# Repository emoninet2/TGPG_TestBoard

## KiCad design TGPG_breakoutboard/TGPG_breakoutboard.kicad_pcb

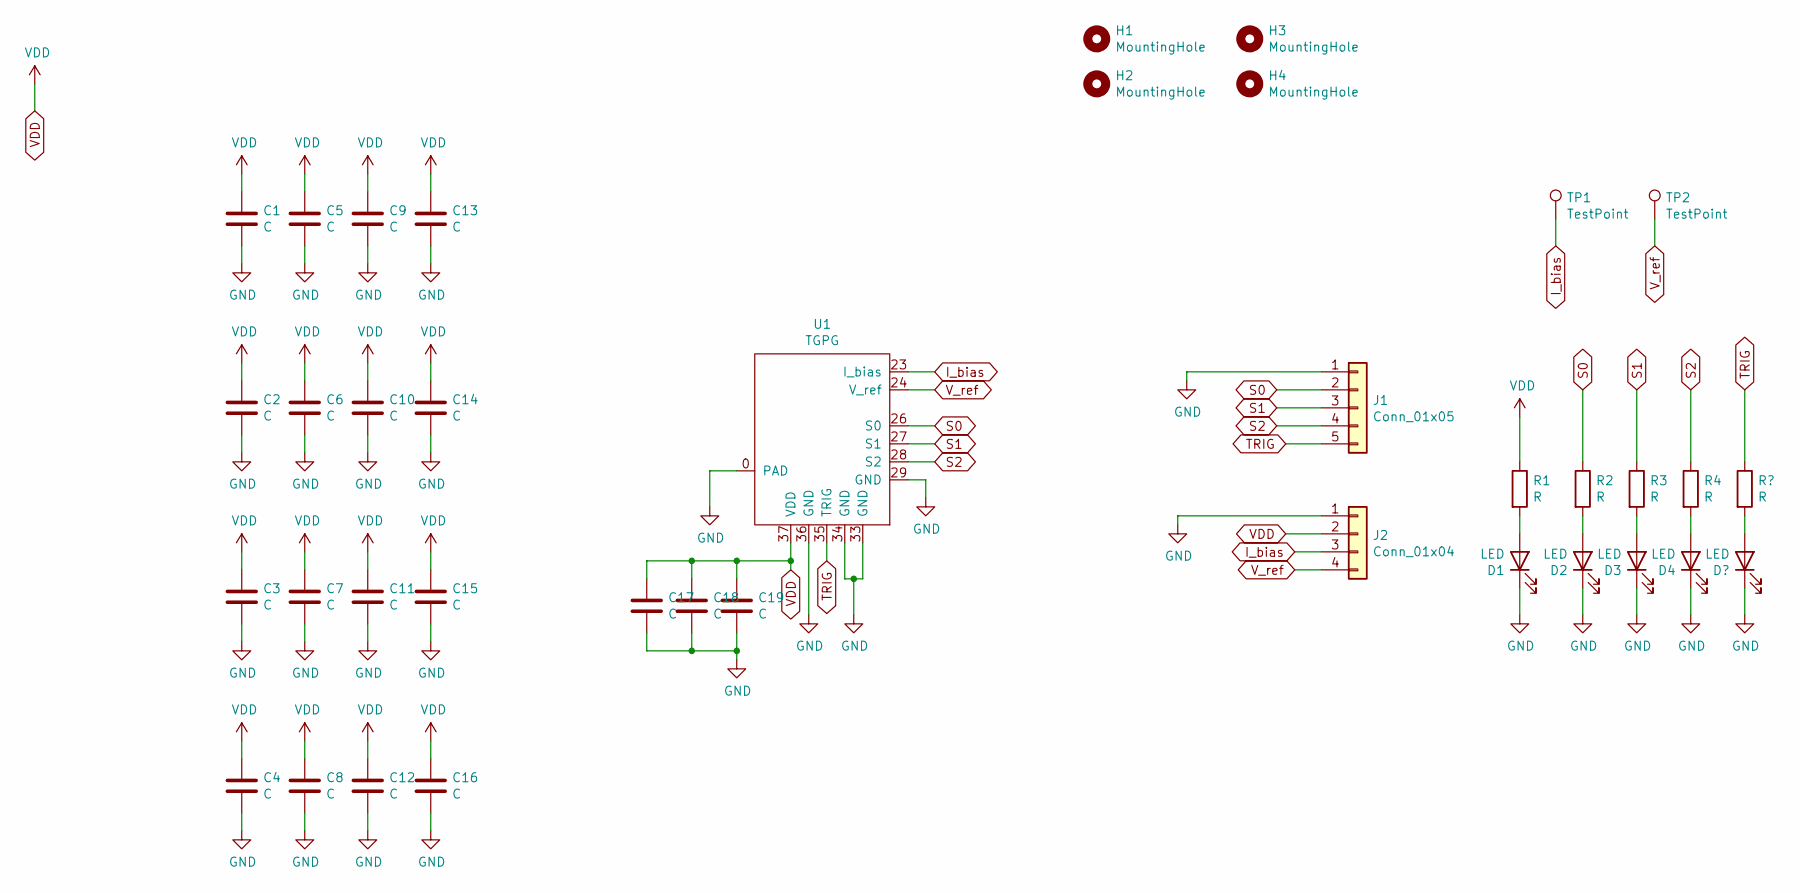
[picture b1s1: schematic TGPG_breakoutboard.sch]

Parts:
C1, C2, C3, C4, C5, C6, C7, C8, C9, C10, C11, C12, C13, C14, C15, C16, C17, C18, C19: C; C_0402_1005Metric
D1, D2, D3, D4: LED; LED_0402_1005Metric
H1, H2, H3, H4: MountingHole; MountingHole_5.5mm_Pad
J1: Conn_01x05; PinHeader_1x05_P2.54mm_Vertical
J2: Conn_01x04; PinHeader_1x04_P2.54mm_Vertical
R1, R2, R3, R4: R; R_0402_1005Metric
TP1, TP2: TestPoint; TestPoint_Pad_1.0x1.0mm
U1: TGPG; Master_w2020

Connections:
GND: C1.2, C2.2, C3.2, C4.2, C5.2, C6.2, C7.2, C8.2, C9.2, C10.2, C11.2, C12.2, C13.2, C14.2, C15.2, C16.2, C17.2, C18.2, C19.2, D1.1 (K), D2.1 (K), D3.1 (K), D4.1 (K), J1.1, J2.1, U1.0 (PAD), U1.29 (GND), U1.33 (GND), U1.34 (GND), U1.36 (GND); also elsewhere on the board
I_bias: J2.3, TP1.1, U1.23 (I_bias)
unnamed: D1.2 (A), R1.2
unnamed: D2.2 (A), R2.2
unnamed: D3.2 (A), R3.2
unnamed: D4.2 (A), R4.2
S0: J1.2, R2.1, U1.26 (S0)
S1: J1.3, R3.1, U1.27 (S1)
S2: J1.4, R4.1, U1.28 (S2)
TRIG: J1.5, U1.35 (TRIG); also elsewhere on the board
VDD: C1.1, C2.1, C3.1, C4.1, C5.1, C6.1, C7.1, C8.1, C9.1, C10.1, C11.1, C12.1, C13.1, C14.1, C15.1, C16.1, C17.1, C18.1, C19.1, J2.2, R1.1, U1.37 (VDD)
V_ref: J2.4, TP2.1, U1.24 (V_ref)

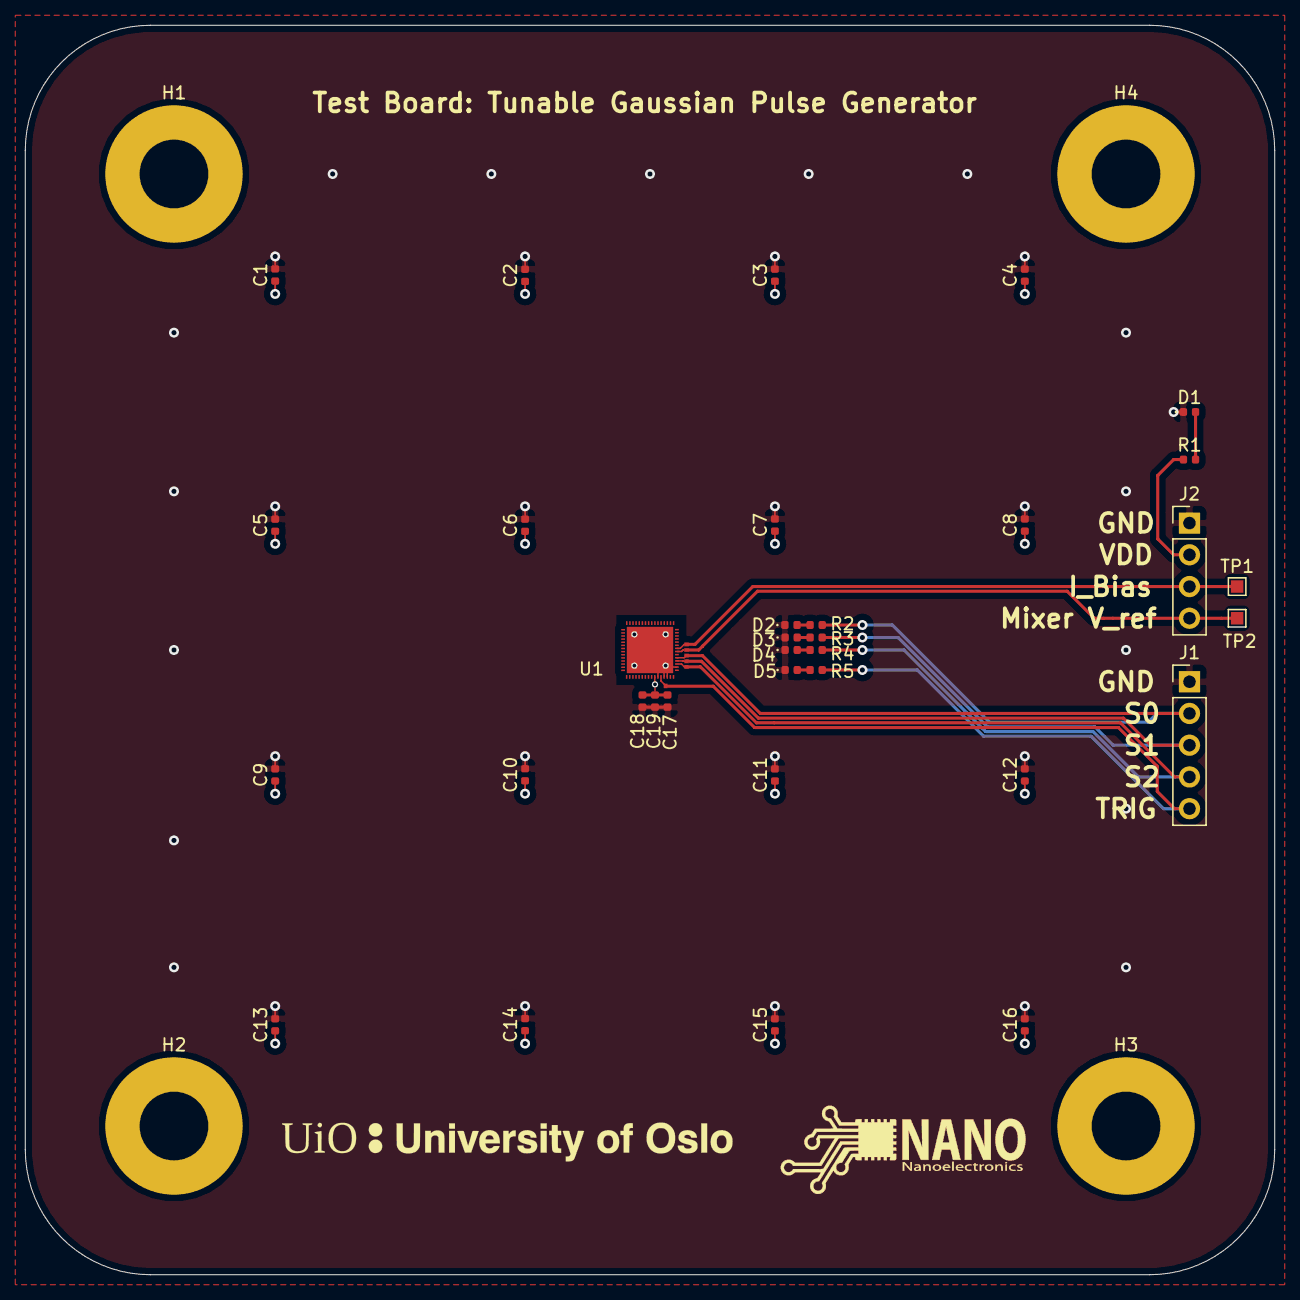
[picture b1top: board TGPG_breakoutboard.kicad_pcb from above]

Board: 4 copper layers, 100.0 x 100.0 mm, 38 parts (0 on the bottom side), 13 nets.

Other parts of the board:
D5: LED; LED_0402_1005Metric
R5: R; R_0402_1005Metric

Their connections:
GND: D5.1; also elsewhere on the board
unnamed: D5.2, R5.2
TRIG: R5.1; also elsewhere on the board

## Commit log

2020-04-19 added existing project
